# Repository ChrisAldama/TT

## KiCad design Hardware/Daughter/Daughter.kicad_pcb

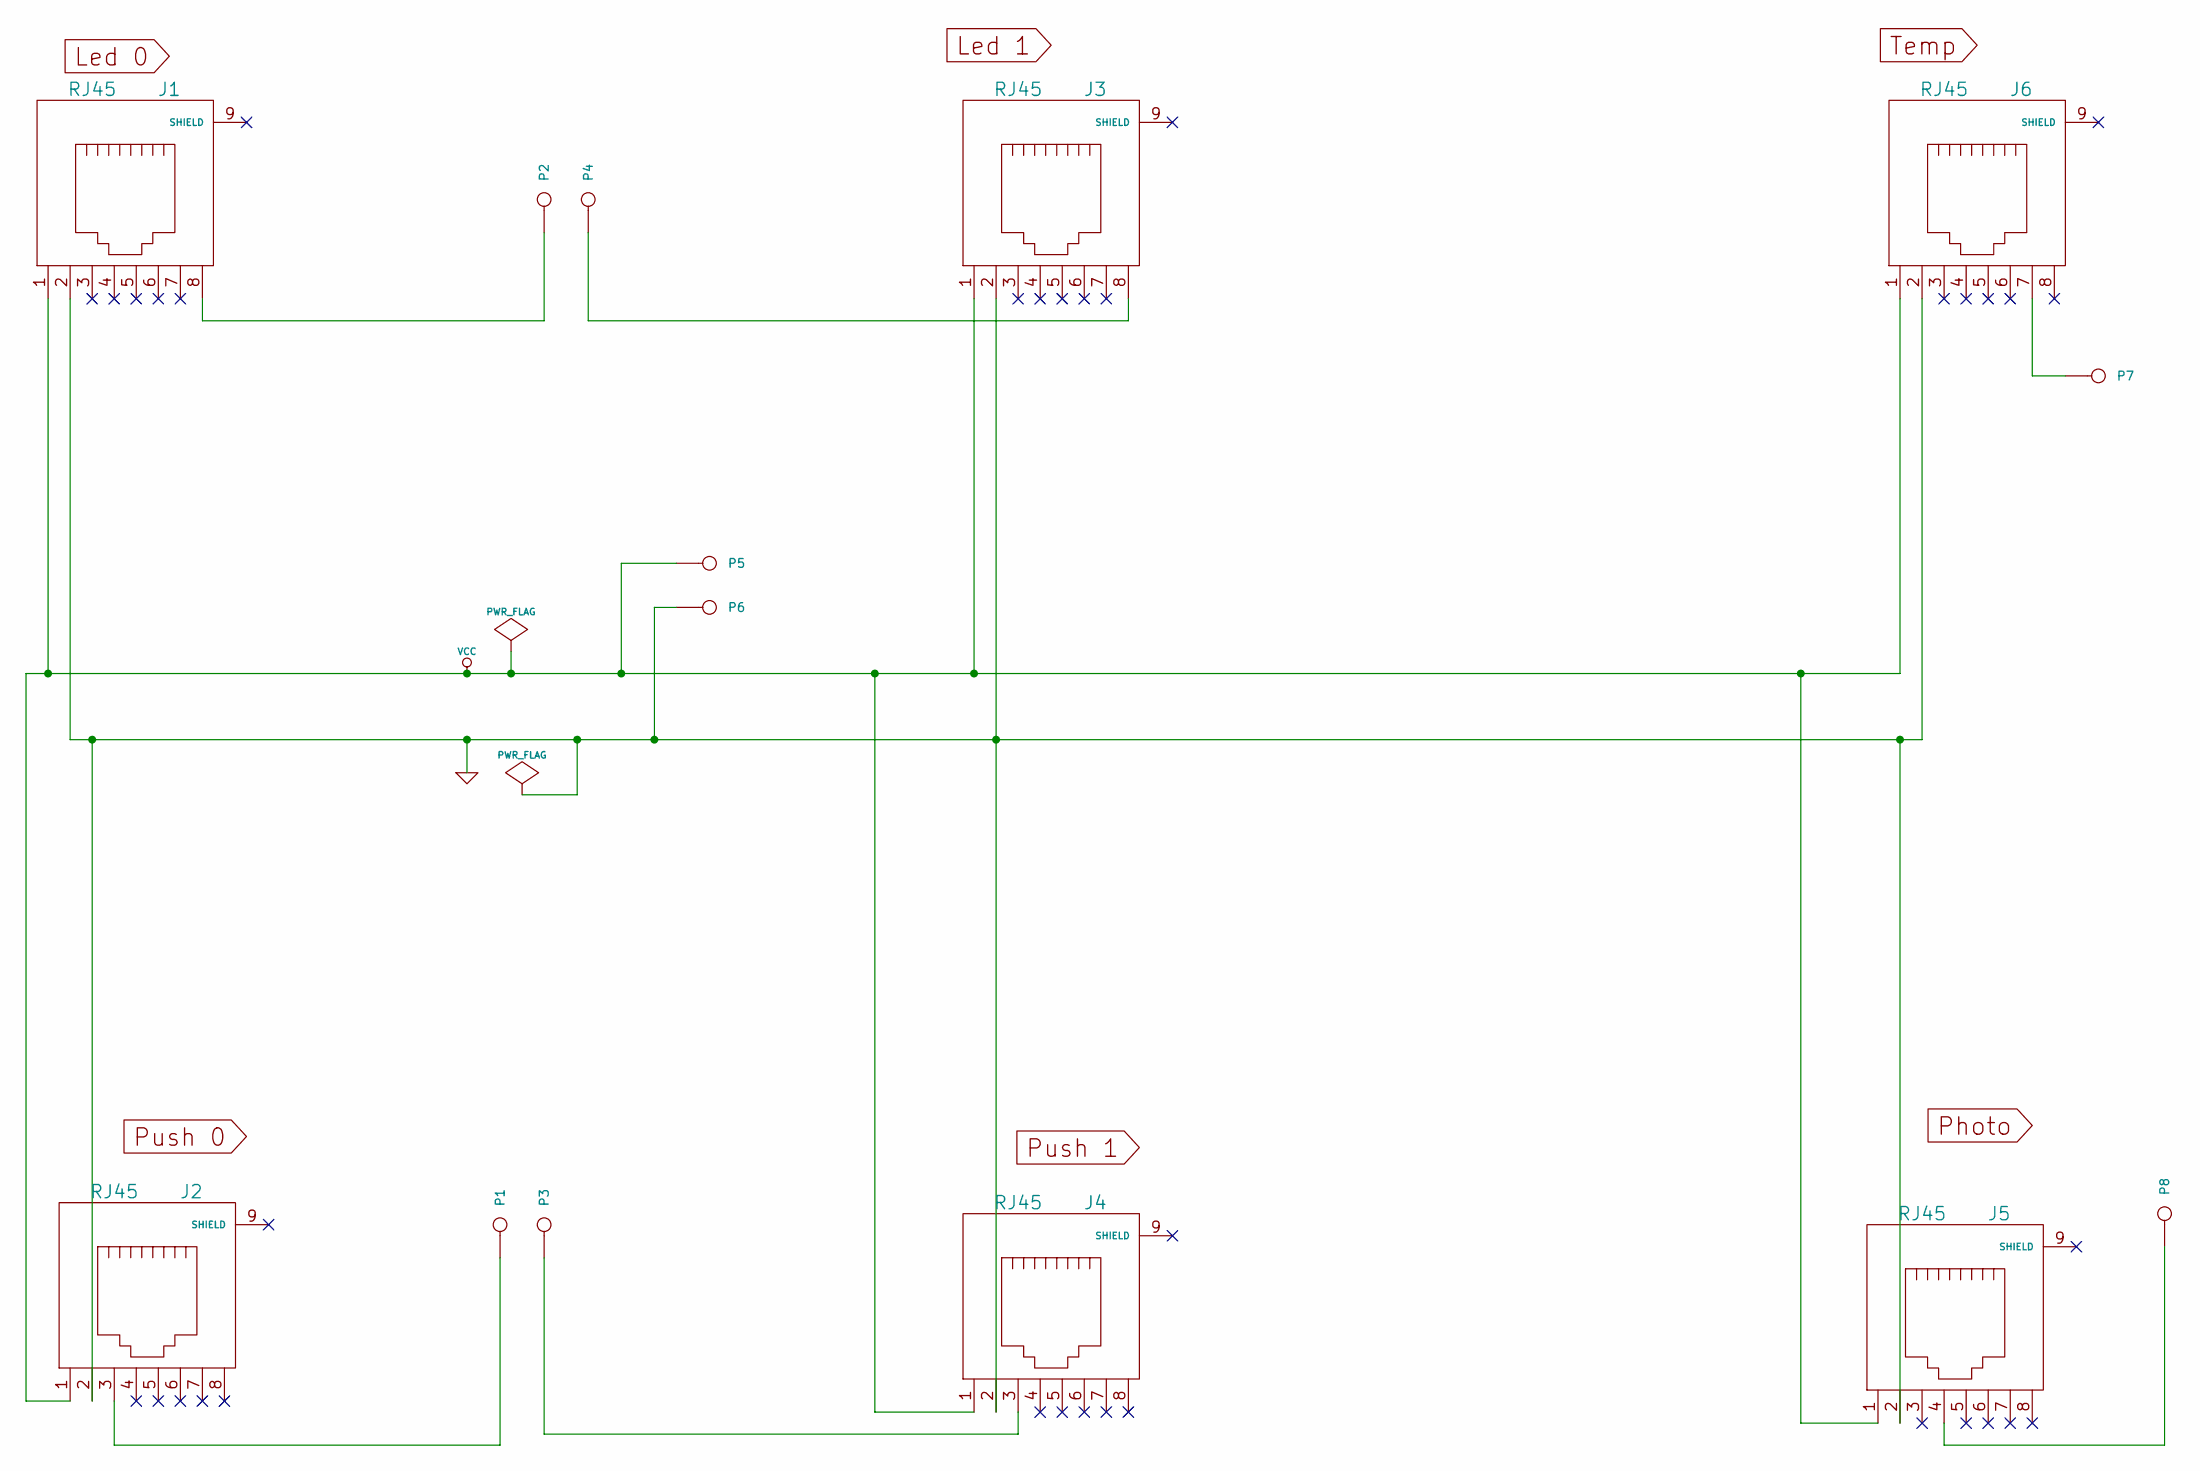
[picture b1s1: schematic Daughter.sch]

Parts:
J1, J2, J3, J4, J5, J6: RJ45
P1, P2, P3, P4, P5, P6, P7, P8: CONN_1

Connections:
GND: J1.2, J2.2, J3.2, J4.2, J5.2, J6.2, P6.1
unnamed: J4.3, P3.1
unnamed: J2.3, P1.1
unnamed: J3.8, P4.1
unnamed: J1.8, P2.1
unnamed: J6.7, P7.1
unnamed: J5.4, P8.1
VCC: J1.1, J2.1, J3.1, J4.1, J5.1, J6.1, P5.1

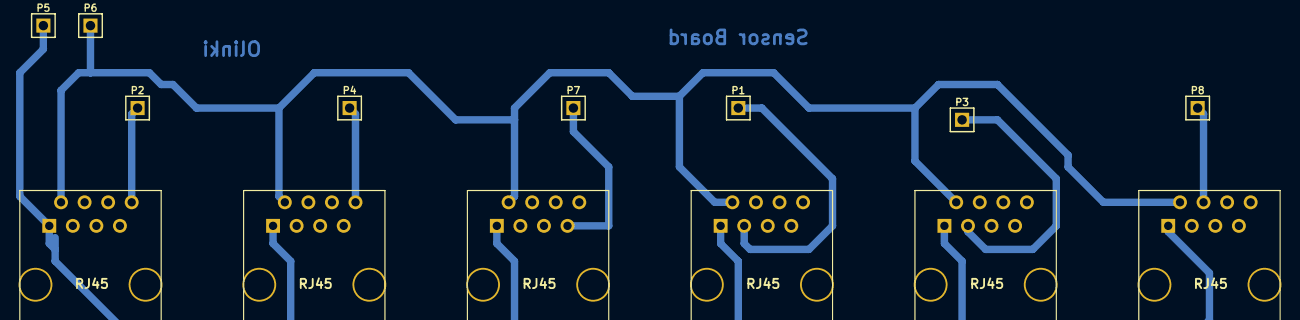
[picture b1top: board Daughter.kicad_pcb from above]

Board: 2 copper layers, 14 parts (0 on the bottom side), 8 nets.

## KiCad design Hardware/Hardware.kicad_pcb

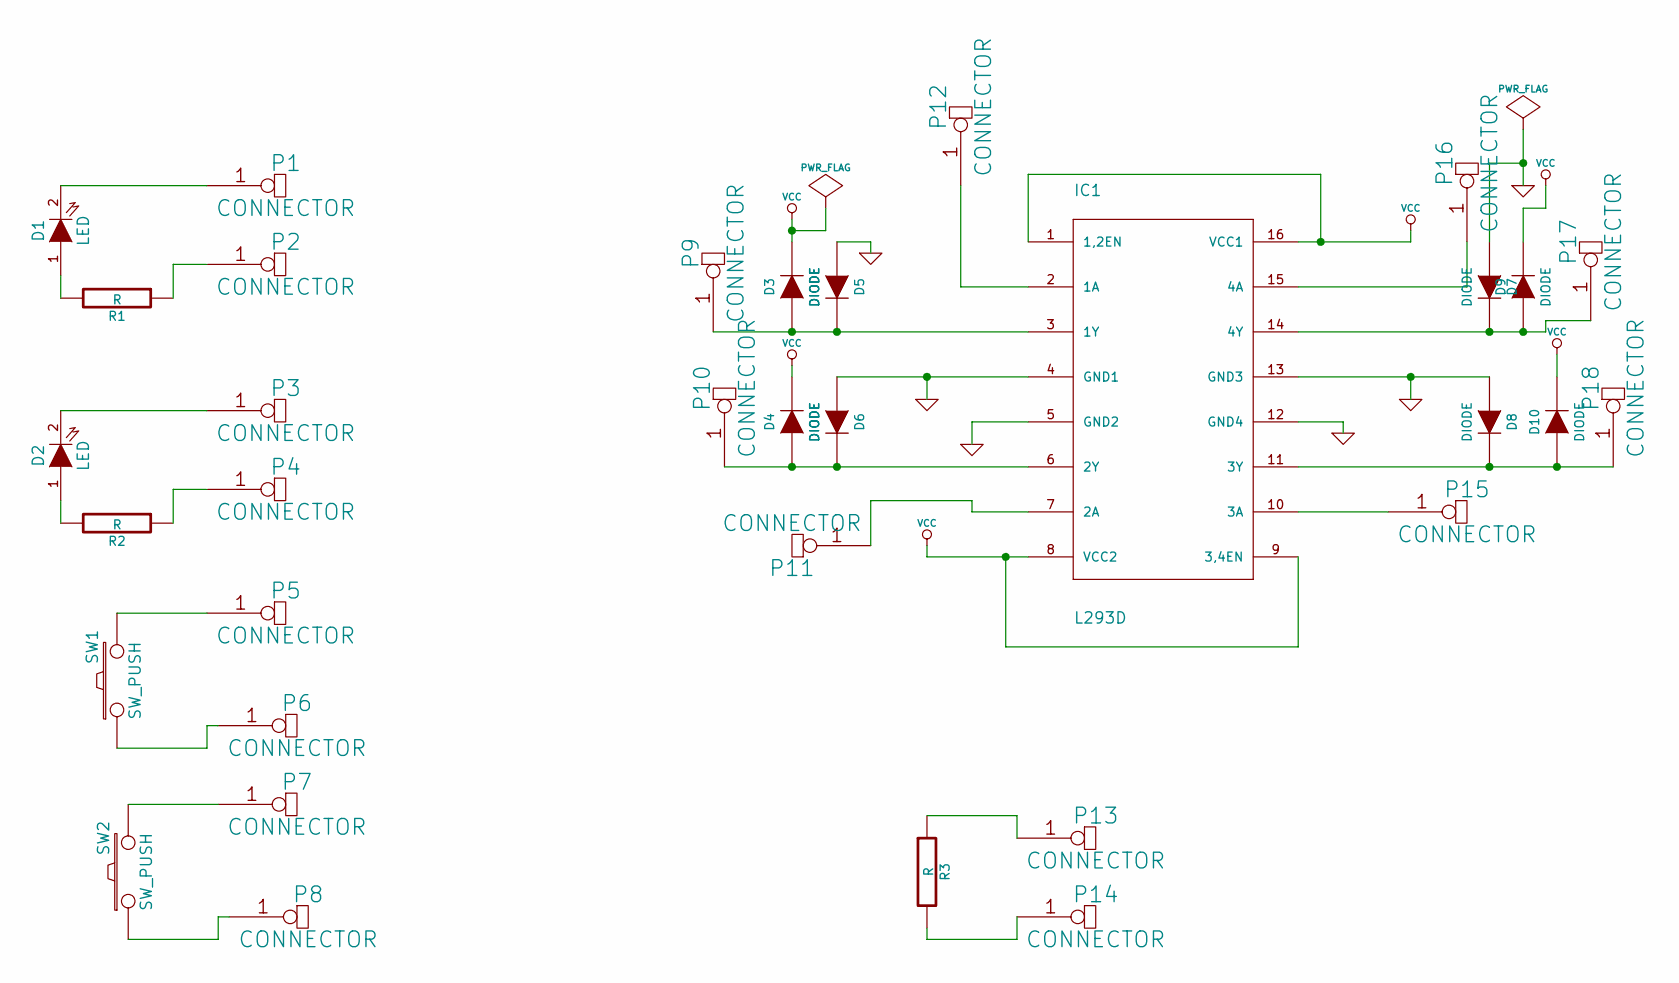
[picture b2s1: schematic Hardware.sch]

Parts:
D1, D2: LED
D3, D4, D5, D6, D7, D8, D9, D10: DIODE
IC1: L293D; stepper drivers-DIL16
P1, P2, P3, P4, P5, P6, P7, P8, P9, P10, P11, P12, P13, P14, P15, P16, P17, P18: CONNECTOR
R1, R2, R3: R
SW1, SW2: SW_PUSH

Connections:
GND: D5.1 (A), D6.1 (A), D7.1 (A), D8.1 (A), IC1.4 (GND1), IC1.5 (GND2), IC1.12 (GND4), IC1.13 (GND3)
unnamed: IC1.2 (1A), P12.1
unnamed: IC1.7 (2A), P11.1
unnamed: IC1.10 (3A), P15.1
unnamed: IC1.15 (4A), P16.1
unnamed: P13.1, R3.1
unnamed: P14.1, R3.2
unnamed: P7.1, SW2.2
unnamed: P4.1, R2.1
unnamed: D2.2 (K), P3.1
unnamed: P5.1, SW1.2
unnamed: P6.1, SW1.1
unnamed: P8.1, SW2.1
unnamed: D1.1 (A), R1.2
unnamed: D1.2 (K), P1.1
unnamed: P2.1, R1.1
unnamed: D2.1 (A), R2.2
unnamed: D3.1 (A), D5.2 (K), IC1.3 (1Y), P9.1
unnamed: D4.1 (A), D6.2 (K), IC1.6 (2Y), P10.1
unnamed: D7.2 (K), D9.1 (A), IC1.14 (4Y), P17.1
unnamed: D8.2 (K), D10.1 (A), IC1.11 (3Y), P18.1
VCC: D3.2 (K), D4.2 (K), D9.2 (K), D10.2 (K), IC1.1 (1,2EN), IC1.8 (VCC2), IC1.9 (3,4EN), IC1.16 (VCC1)

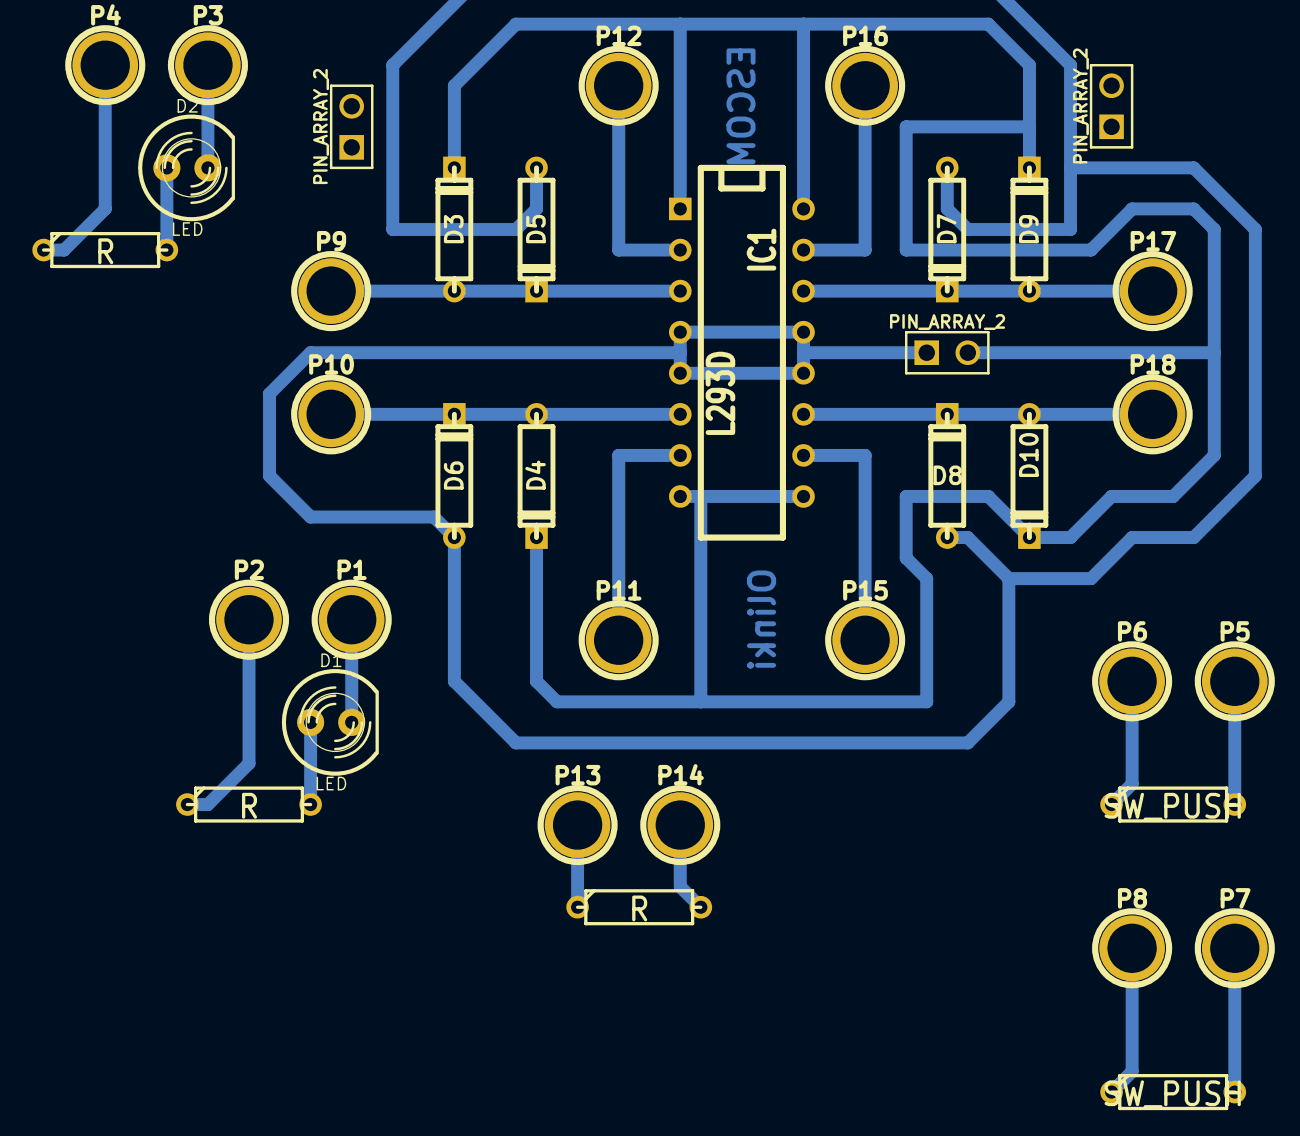
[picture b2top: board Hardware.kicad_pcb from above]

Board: 2 copper layers, 37 parts (0 on the bottom side), 22 nets.

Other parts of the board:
PIN_ARRAY_2, PIN_ARRAY_2#2, PIN_ARRAY_2#3: Val**; PIN_ARRAY_2X1

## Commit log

2014-11-27 Instrucciones
2015-08-17 html interface
2015-08-20 p logica
2015-11-13 almost ready
2015-11-13 Autocontenido
2015-11-13 Pfin sibling
2015-11-13 Fixing Windows building, inserting after end
2015-11-14 sensors
2015-11-15 Fixed console, app - arduino by serial
2015-11-15 Serial debuggin
2015-11-15 Analog fixed, Temp with error
2015-11-17 Fixing Coompiling on older GCC versions
2015-11-17 Fixing Compiling on older GCC versions
2015-11-17 Fixing Compiling on older GCC versions(4.6)
2015-11-17 Zoom Zoom Zoom
2015-11-17 Close shorcut
2015-11-17 Fix zoom
2015-12-07 final
